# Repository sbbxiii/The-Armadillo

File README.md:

# 🛡️ The Armadillo: Custom ATmega328P + TMC2209 Stepper Motor Controller PCB

---

## 1. Executive Summary

**The Armadillo** is an open-source, Arduino-compatible motion control PCB designed from first principles in **KiCad 10.0.1**. It pairs the reliable **Microchip ATmega328P** 8-bit AVR microcontroller with the high-performance **Trinamic TMC2209-LA** silent bipolar stepper motor driver on a rugged $60.0\text{ mm} \times 60.0\text{ mm}$ 2-layer FR-4 board.

Featuring an onboard **WCH CH340K** USB-to-UART converter with automated DTR auto-reset, The Armadillo provides seamless plug-and-play programming directly through the Arduino IDE, PlatformIO, or AVR-GCC toolchains. Key features include silent stepper motion via **StealthChop2™**, sensorless homing via **StallGuard4™**, dynamic runtime current tuning over a single-wire **PD_UART** interface, and hardware RC-filtered sensor inputs.

---

## 2. 3D Raytraced Visualizations

<p align="center">
  <br>
  <em>Figure 1: Raytraced 3D perspective view of The Armadillo motor controller board showing the ATmega328P core, TMC2209 driver, and screw terminal I/O.</em>
</p>

| Top View (Silicon, Connectors & SMT Layout) | Bottom View (Solid Ground Return & Driver Thermal Vias) |
| :---: | :---: |
|  |  |

---

## 3. Circuit Architecture & Block Diagram

```mermaid
flowchart TD
    subgraph Power_Subsystem ["Power Distribution Network (PDN)"]
        VIN["Motor Power (4.75V - 29V)<br/>Terminal Block J8"] --> BulkCap["Bulk Decoupling<br/>100µF Radial + 2x 100nF"]
        BulkCap --> VMOT["VMOT Supply Rail"]
        VMOT --> LDO["NCP1117-5.0 LDO<br/>(Steps to +5V Logic)"]
        USB["USB Type-B Port (J2)"] --> Schottky["SS14 Schottky Diode (D3)"]
        Schottky --> VCC5["+5V System VCC Rail"]
        LDO --> VCC5
    end

    subgraph MCU_Subsystem ["Microcontroller & Communications"]
        VCC5 --> MCU["ATmega328P-A (TQFP-32)<br/>16.000 MHz Clock"]
        CH340["CH340K USB-UART (U2)"] <-->|"UART RX/TX + DTR Reset"| MCU
        ICSP["6-Pin AVR ISP Header (J1)"] <-->|"SPI MOSI/MISO/SCK/RST"| MCU
        MCU --> LEDS["Power & Diagnostic LEDs<br/>(D1, D2)"]
    end

    subgraph Motion_Subsystem ["Silent Motion Control"]
        VMOT --> TMC["Trinamic TMC2209-LA (U3)<br/>Silent Stepper Driver"]
        VCC5 --> TMC
        MCU -->|"M1_STEP / M1_DIR / EN"| TMC
        MCU <-->|"PD_UART (Single-Wire)"| TMC
        TMC --> SenseRes["Dual 0.11Ω 1210 Sense Resistors<br/>(R13, R14)"]
        TMC --> MotorOut["4-Phase Stepper Terminal (J7)<br/>(A1, A2, B1, B2)"]
    end

    subgraph IO_Subsystem ["Filtered Sensor Inputs"]
        Sensors["Endstops / Sensors (J3 - J6)"] --> RCFilt["RC Low-Pass Filters<br/>(1.5kΩ + 100nF)"]
        RCFilt --> MCU
    end
```

---

## 4. Hardware Specifications & Feature Matrix

### Electrical & Mechanical Metrics
| Specification | Parameter Value | Engineering Notes |
| :--- | :--- | :--- |
| **Board Footprint** | $60.00\text{ mm} \times 60.00\text{ mm}$ | Compact square profile with 3.0 mm radius rounded corners |
| **Mounting Pattern** | 4× M3 Mounting Holes | Positioned at corners for rigid enclosure mounting |
| **Layer Stackup** | 2-Layer FR-4 (1.6 mm thickness) | Top signal/routing + solid bottom GND return plane |
| **Motor Input Voltage ($V_S$)** | **4.75V to 29.0V DC** | Accepts standard 12V or 24V industrial/3D-printer power supplies |
| **Motor Peak Current** | **2.8A Peak / 2.0A RMS** | Configurable in software via TMC2209 internal registers |
| **Current Sense Resistors** | Dual $0.11\ \Omega \pm 1\%$ (1210 SMT) | High power dissipation footprint for thermal stability |
| **Microstepping Modes** | Up to **1/256** | Native 1/16 with MicroPlyer™ interpolation to 1/256 |
| **Microcontroller** | ATmega328P-A (TQFP-32) | 32 KB Flash, 2 KB SRAM, 1 KB EEPROM @ 16 MHz |
| **USB Interface** | CH340K (SSOP-10) | Built-in clock, requires no external crystal |
| **Design Rule Check (DRC)** | **0 Errors, 0 Unconnected Items** | 100% compliant with standard 2-layer PCB fabrication rules |

---

## 5. Trinamic TMC2209 Key Technologies

1. **StealthChop2™**: Voltage-regulated chopper providing completely silent motor movement at low and medium velocities. Eliminates motor whine.
2. **SpreadCycle™**: Highly dynamic current control chopper mode that delivers high torque and precise microstepping at high step frequencies.
3. **StallGuard4™**: Real-time sensorless load measurement that detects mechanical endstops by monitoring motor back-EMF, eliminating mechanical limit switches.
4. **Single-Wire PD_UART**: Allows the ATmega328P to dynamically tune drive current, chopper thresholds, microstep resolution, and read motor diagnostics via one GPIO pin.

---

## 6. Pinout & Peripheral Mapping

### Microcontroller Pin Mapping
| ATmega328P Pin | Net Name | Hardware Function / Target Peripheral |
| :---: | :--- | :--- |
| **Pin 1 (PD3)** | `M1_STEP` | Step pulse command to TMC2209 Pin 16 |
| **Pin 2 (PD4)** | `M1_DIR` | Direction pulse command to TMC2209 Pin 17 |
| **Pin 9 (PB6)** | `XTAL1` | 16.000 MHz Crystal Oscillator ($Y1$) |
| **Pin 10 (PB7)** | `XTAL2` | 16.000 MHz Crystal Oscillator ($Y1$) |
| **Pin 11 (PD5)** | `EN` | Motor output enable/disable (active low) to TMC2209 Pin 18 |
| **Pin 12 (PD6)** | `PD_UART` | Half-duplex single-wire UART communication with TMC2209 Pin 20 |
| **Pin 13 (PD7)** | `DIAGNOSTIC` | StallGuard / fault flag input from TMC2209 Pin 22 |
| **Pin 15 (PB1)** | `DIGITAL_IN1` | Filtered digital input via header $J5$ (RC filtered) |
| **Pin 16 (PB2)** | `DIGITAL_IN2` | Filtered digital input via header $J6$ (RC filtered) |
| **Pin 17 (PB3)** | `MOSI` | SPI Master Out / In-System Programming ($J1$) |
| **Pin 18 (PB4)** | `MISO` | SPI Master In / In-System Programming ($J1$) |
| **Pin 19 (PB5)** | `SCK` | SPI Clock / In-System Programming ($J1$) |
| **Pin 23 (PC0)** | `ANALOG_IN3` | Filtered analog/digital input via header $J3$ |
| **Pin 24 (PC1)** | `ANALOG_IN4` | Filtered analog/digital input via header $J4$ |
| **Pin 29 (PC6)** | `RESET` | Active-low reset tied to tactile switch $SW1$ and CH340K DTR line |
| **Pin 30 (PD0)** | `RXD` (`UART-`) | Hardware UART receive from CH340K USB bridge |
| **Pin 31 (PD1)** | `TXD` (`UART+`) | Hardware UART transmit to CH340K USB bridge |

### External Connectors
| Connector | Type | Net Connections | Function |
| :--- | :--- | :--- | :--- |
| **J1** | 2×3 2.54mm Header | MOSI, MISO, SCK, RESET, VCC, GND | Standard AVR ICSP programming port |
| **J2** | USB Type-B Female | VBUS, D-, D+, GND | PC programming and USB serial communication |
| **J3** | 1×3 2.54mm Header | VCC, `ANALOG_IN3` (filtered), GND | Sensor / Potentiometer input |
| **J4** | 1×3 2.54mm Header | VCC, `ANALOG_IN4` (filtered), GND | Sensor / Limit switch input |
| **J5** | 1×3 2.54mm Header | VCC, `DIGITAL_IN1` (filtered), GND | Optical / Mechanical Endstop input |
| **J6** | 1×3 2.54mm Header | VCC, `DIGITAL_IN2` (filtered), GND | Optical / Mechanical Endstop input |
| **J7** | 4-Pin 2.54mm Screw Terminal | Motor Coils: `A1`, `A2`, `B1`, `B2` | Stepper motor phase output |
| **J8** | 2-Pin 3.5mm Screw Terminal | `VIN` ($4.75\text{V} - 29\text{V}$), `GND` | Main motor power supply input |

---

## 7. Deliverables & Production Assets

| Asset Category | File Path | Description |
| :--- | :--- | :--- |
| **Schematic Vector PDF** | [`schematic/ATmega_TMC2209_Schematic.pdf`](schematic/ATmega_TMC2209_Schematic.pdf) | High-resolution printable schematic |
| **Schematic Vector SVG** | [`schematic/ATmega_TMC2209_Schematic.svg`](schematic/ATmega_TMC2209_Schematic.svg) | Scalable vector graphic of complete circuit |
| **Bill of Materials** | [`manufacturing/ATmega_TMC2209_BOM.csv`](manufacturing/ATmega_TMC2209_BOM.csv) | Full component list with footprints and quantities |
| **Fabrication Package** | [`manufacturing/ATmega_TMC2209_Gerbers_Rev1.zip`](manufacturing/ATmega_TMC2209_Gerbers_Rev1.zip) | Production gerbers & Excellon drill file |
| **KiCad 10 Project** | [`hardware/`](hardware/) | Native `.kicad_pro`, `.kicad_sch`, and `.kicad_pcb` CAD files |

---

## 8. Author & License

* **Designed & Engineered by:** Osakwe Nmesoma Chukwukadibia ([@sbbxiii](https://github.com/sbbxiii))
* **License:** [MIT License](LICENSE)

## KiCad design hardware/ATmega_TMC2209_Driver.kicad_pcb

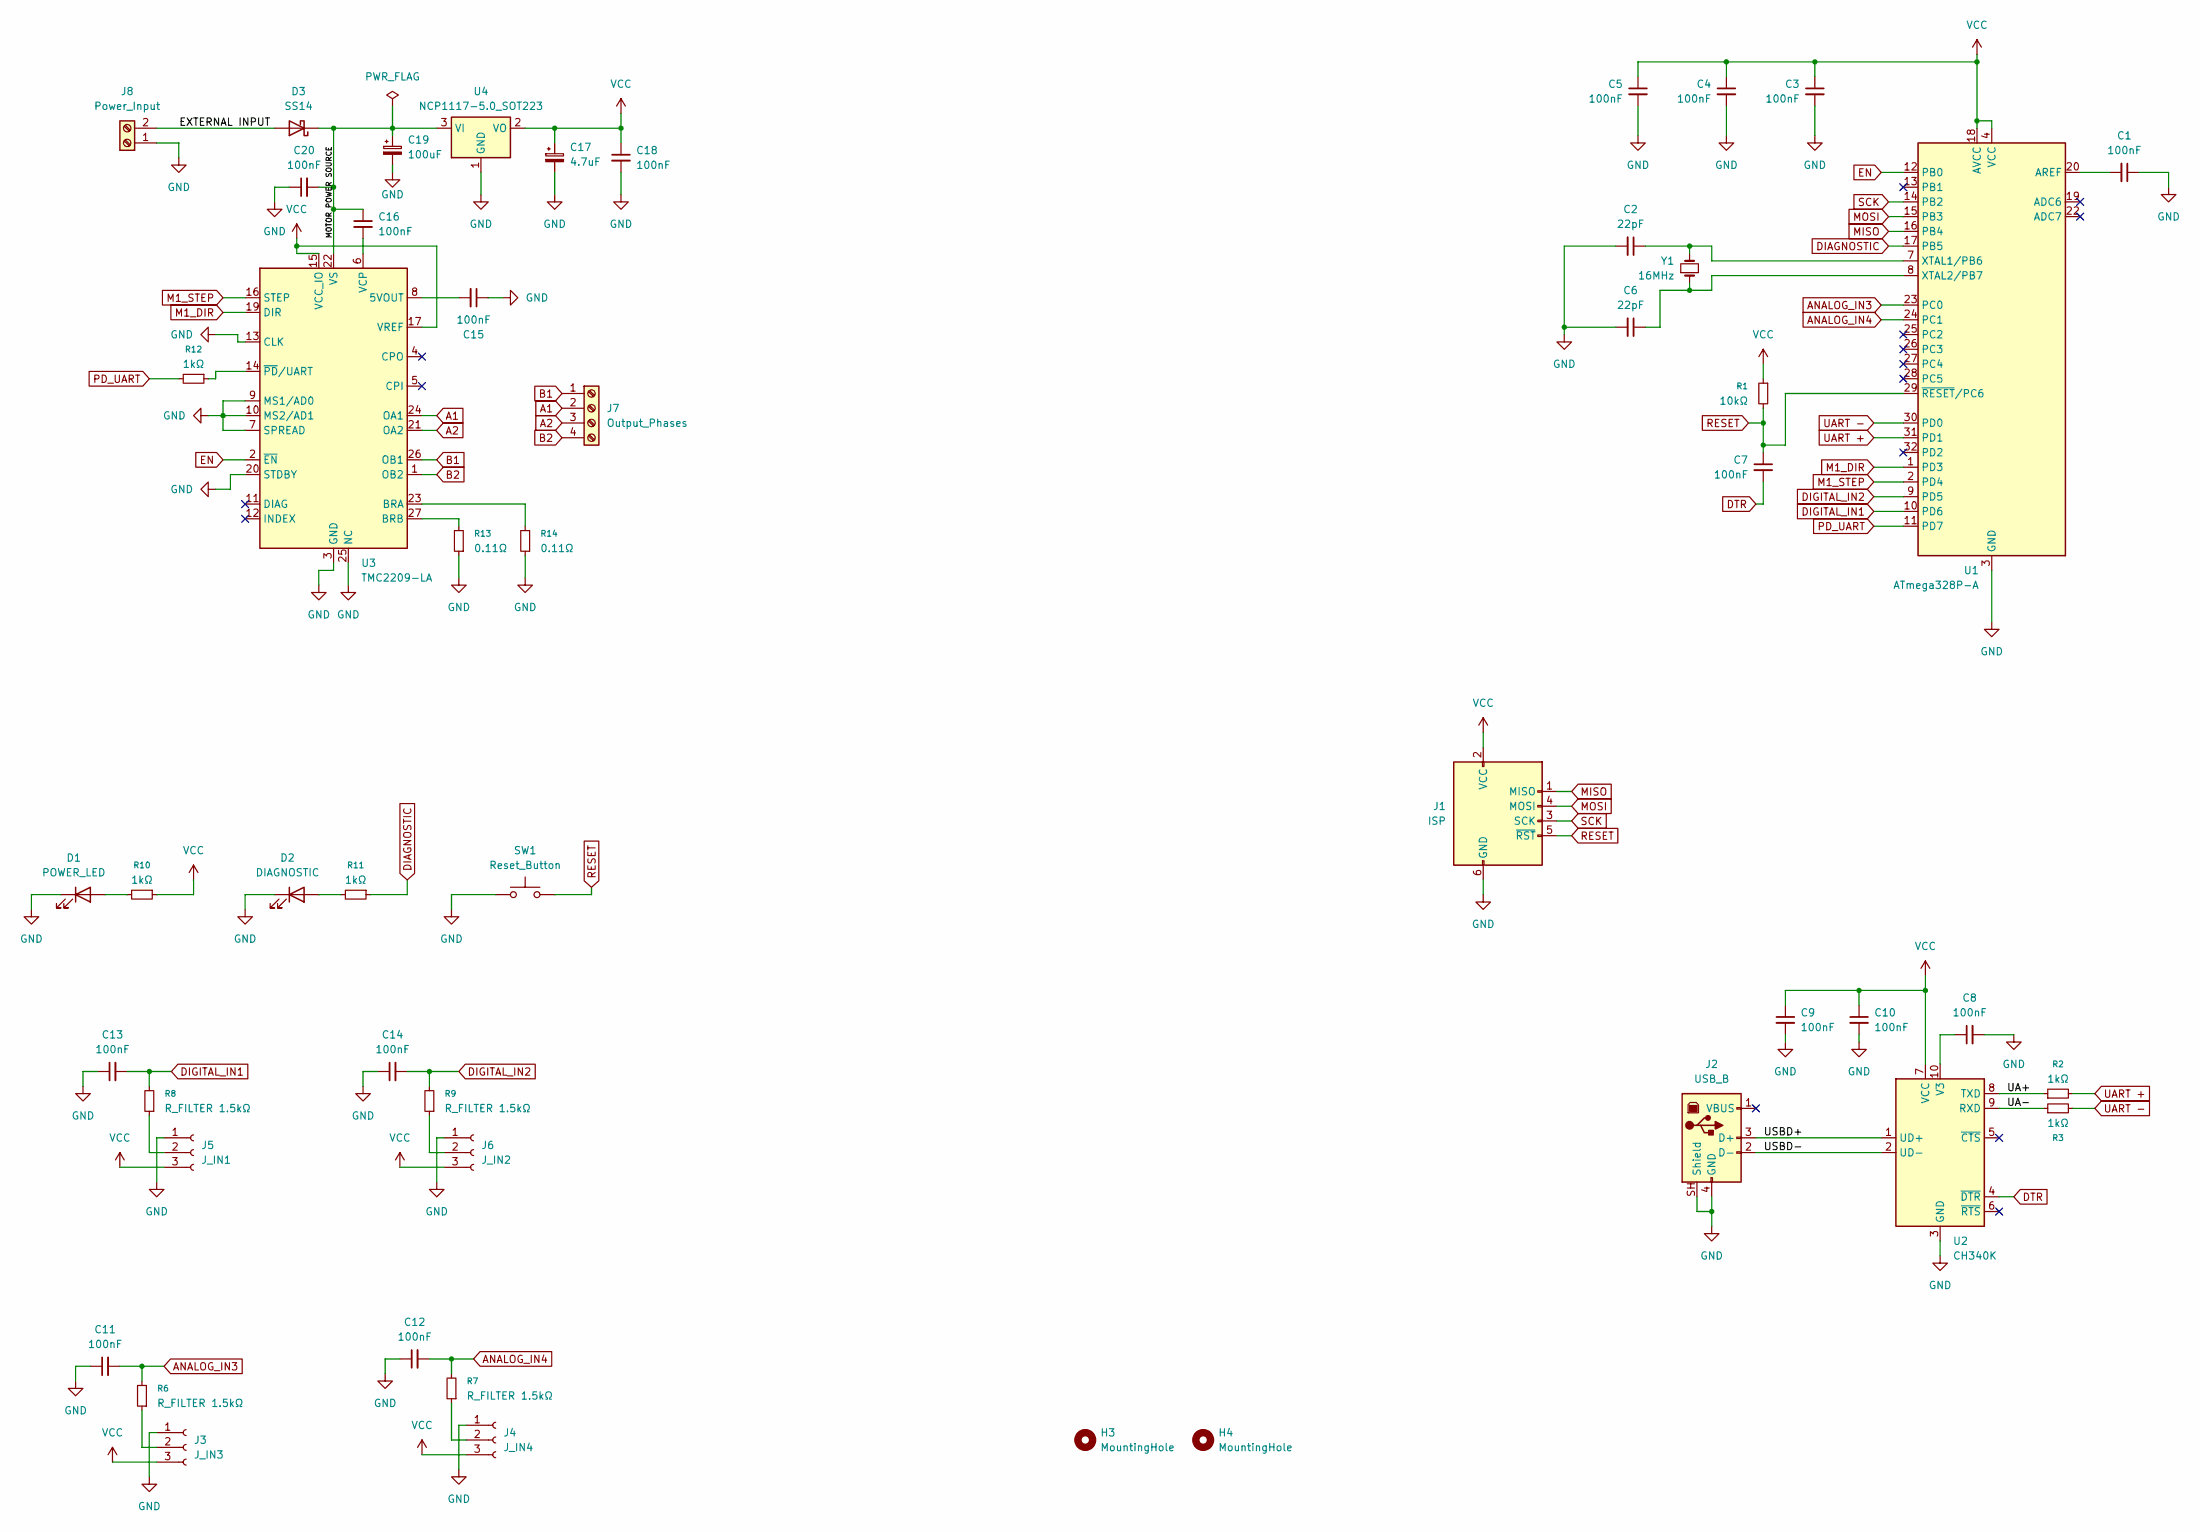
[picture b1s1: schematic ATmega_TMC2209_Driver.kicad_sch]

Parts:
C1, C3, C4, C5, C7, C8, C9, C10, C11, C12, C13, C14, C15, C16, C18, C20: 100nF; C_0805_2012Metric
C2, C6: 22pF; C_0805_2012Metric
C17: 4.7uF; CP_Elec_4x5.3
C19: 100uF; CP_Radial_D8.0mm_P3.50mm
D1: POWER_LED; LED_0805_2012Metric
D2: DIAGNOSTIC; LED_0805_2012Metric
D3: SS14; D_SMA
H3, H4: MountingHole; MountingHole_2.2mm_M2_Pad
J1: ISP; PinHeader_2x03_P2.54mm_Vertical
J2: USB_B; USB_B_OST_USB-B1HSxx_Horizontal
J3: J_IN3; PinHeader_1x03_P2.54mm_Vertical
J4: J_IN4; PinHeader_1x03_P2.54mm_Vertical
J5: J_IN1; PinHeader_1x03_P2.54mm_Vertical
J6: J_IN2; PinHeader_1x03_P2.54mm_Vertical
J7: Output_Phases; TerminalBlock_Phoenix_MPT-0,5-4-2.54_1x04_P2.54mm_Horizontal
J8: Power_Input; TerminalBlock_Phoenix_PT-1,5-2-3.5-H_1x02_P3.50mm_Horizontal
R1: 10kΩ; R_0805_2012Metric
R2, R3, R10, R11, R12: 1kΩ; R_0805_2012Metric
R6, R7, R8, R9: R_FILTER 1.5kΩ; R_0805_2012Metric
R13, R14: 0.11Ω; R_1210_3225Metric
SW1: Reset_Button; SW_SPST_TS-1088-xR020
U1: ATmega328P-A; TQFP-32_7x7mm_P0.8mm
U2: CH340K; SSOP-10-1EP_3.9x4.9mm_P1mm_EP2.1x3.3mm
U3: TMC2209-LA; VQFN-28-1EP_5x5mm_P0.5mm_EP3.7x3.7mm_ThermalVias
U4: NCP1117-5.0_SOT223; SOT-223-3_TabPin2
Y1: 16MHz; Crystal_SMD_5032-2Pin_5.0x3.2mm

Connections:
/EXTERNAL INPUT: D3.2 (A), J8.2
/MOTOR POWER SOURCE: C16.1, C19.1, C20.2, D3.1 (K), U3.22 (VS), U3.28 (VS), U4.3 (VI)
/UA+: R2.1, U2.8 (TXD)
/UA-: R3.1, U2.9 (RXD)
/USBD+: J2.3 (D+), U2.1 (UD+)
/USBD-: J2.2 (D-), U2.2 (UD-)
A1: J7.2, U3.24 (OA1)
A2: J7.3, U3.21 (OA2)
ANALOG_IN3: C11.2, R6.2, U1.23 (PC0)
ANALOG_IN4: C12.2, R7.2, U1.24 (PC1)
B1: J7.1, U3.26 (OB1)
B2: J7.4, U3.1 (OB2)
DIAGNOSTIC: R11.1, U1.17 (PB5)
DIGITAL_IN1: C13.2, R8.2, U1.10 (PD6)
DIGITAL_IN2: C14.2, R9.2, U1.9 (PD5)
DTR: C7.2, U2.4 (~DTR)
EN: U1.12 (PB0), U3.2 (~EN)
GND: C1.1, C2.2, C3.2, C4.2, C5.2, C6.2, C8.2, C9.2, C10.2, C11.1, C12.1, C13.1, C14.1, C15.1, C17.2, C18.2, C19.2, C20.1, D1.1 (K), D2.1 (K), J1.6 (GND), J2.4 (GND), J2.SH (Shield), J3.1, J4.1, J5.1, J6.1, J8.1, R13.1, R14.1, SW1.1, U1.3 (GND), U1.5 (GND), U1.21 (GND), U2.3 (GND), U2.11 (GND), U3.3 (GND), U3.7 (SPREAD), U3.9 (MS1/AD0), U3.10 (MS2/AD1), U3.13 (CLK), U3.18 (GND), U3.20 (STDBY), U3.25 (NC), U3.29 (GND), U4.1 (GND)
M1_DIR: U1.1 (PD3), U3.19 (DIR)
M1_STEP: U1.2 (PD4), U3.16 (STEP)
MISO: J1.1 (MISO), U1.16 (PB4)
MOSI: J1.4 (MOSI), U1.15 (PB3)
unnamed: D1.2 (A), R10.2
unnamed: D2.2 (A), R11.2
unnamed: J3.2, R6.1
unnamed: J4.2, R7.1
unnamed: J5.2, R8.1
unnamed: J6.2, R9.1
unnamed: C1.2, U1.20 (AREF)
unnamed: C2.1, U1.7 (XTAL1/PB6), Y1.2
unnamed: C6.1, U1.8 (XTAL2/PB7), Y1.1
unnamed: C8.1, U2.10 (V3)
unnamed: C15.2, U3.8 (5VOUT)
unnamed: R14.2, U3.23 (BRA)
unnamed: R13.2, U3.27 (BRB)
unnamed: C16.2, U3.6 (VCP)
unnamed: R12.1, U3.14 (~PD/UART)
PD_UART: R12.2, U1.11 (PD7)
RESET: C7.1, J1.5 (~RST), R1.2, SW1.2, U1.29 (~RESET/PC6)
SCK: J1.3 (SCK), U1.14 (PB2)
UART +: R2.2, U1.31 (PD1)
UART -: R3.2, U1.30 (PD0)
VCC: C3.1, C4.1, C5.1, C9.1, C10.1, C17.1, C18.1, J1.2 (VCC), J3.3, J4.3, J5.3, J6.3, R1.1, R10.1, U1.4 (VCC), U1.6 (VCC), U1.18 (AVCC), U2.7 (VCC), U3.15 (VCC_IO), U3.17 (VREF), U4.2 (VO)

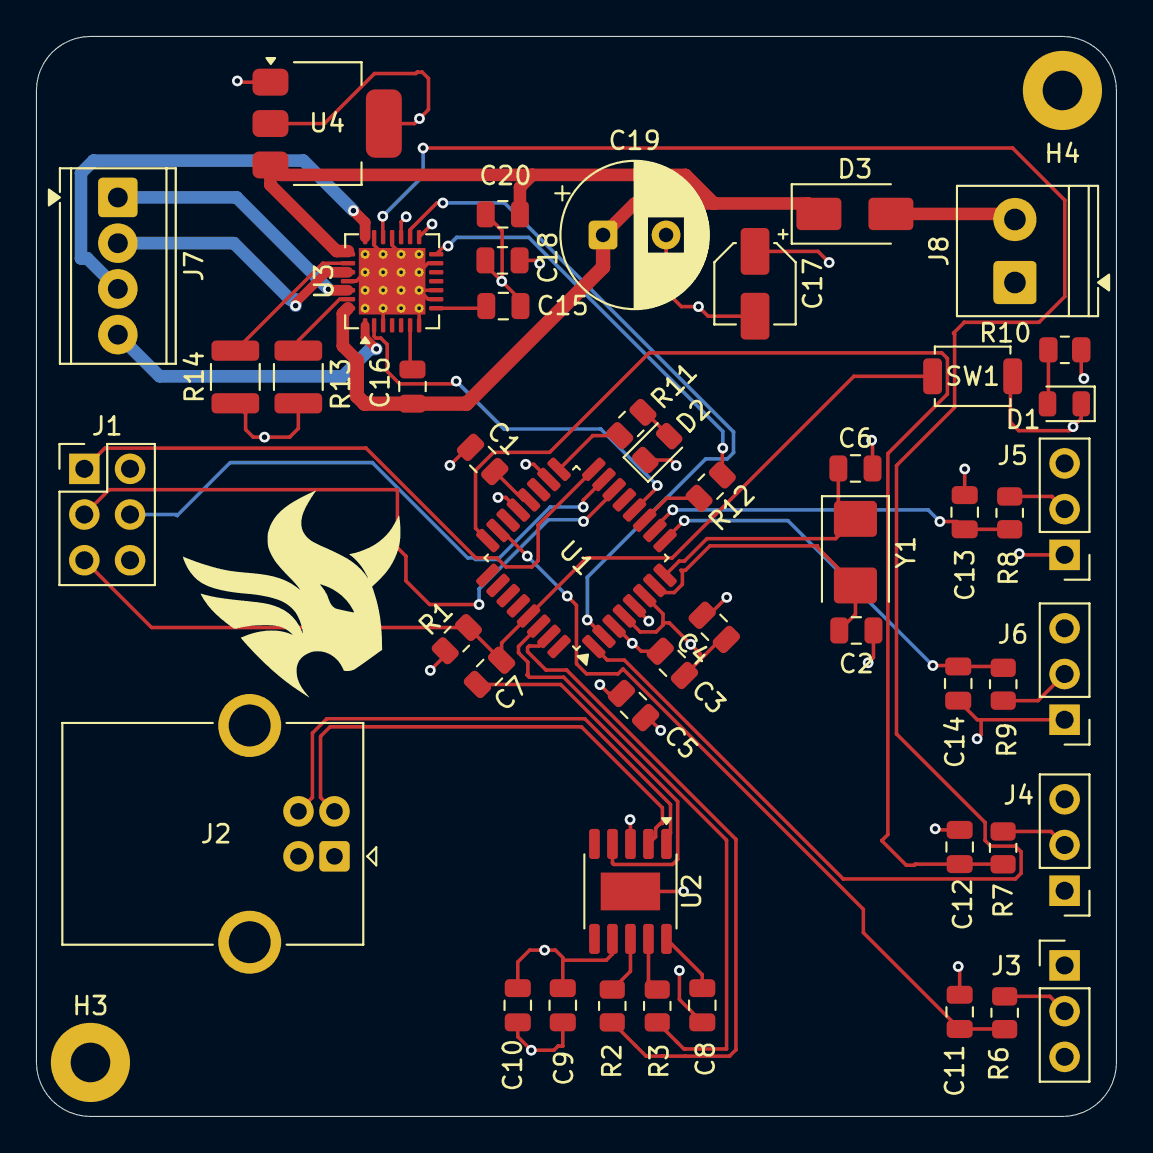
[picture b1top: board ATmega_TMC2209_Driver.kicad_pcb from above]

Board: 4 copper layers, 60.0 x 60.0 mm, 51 parts (0 on the bottom side), 43 nets.

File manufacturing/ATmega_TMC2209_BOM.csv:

"Refs","Value","Footprint","Qty","DNP"
"C1","100nF","Capacitor_SMD:C_0805_2012Metric","1",""
"C2","22pF","Capacitor_SMD:C_0805_2012Metric","1",""
"C3","100nF","Capacitor_SMD:C_0805_2012Metric","1",""
"C4","100nF","Capacitor_SMD:C_0805_2012Metric","1",""
"C5","100nF","Capacitor_SMD:C_0805_2012Metric","1",""
"C6","22pF","Capacitor_SMD:C_0805_2012Metric","1",""
"C7","100nF","Capacitor_SMD:C_0805_2012Metric","1",""
"C8","100nF","Capacitor_SMD:C_0805_2012Metric","1",""
"C9","100nF","Capacitor_SMD:C_0805_2012Metric","1",""
"C10","100nF","Capacitor_SMD:C_0805_2012Metric","1",""
"C11","100nF","Capacitor_SMD:C_0805_2012Metric","1",""
"C12","100nF","Capacitor_SMD:C_0805_2012Metric","1",""
"C13","100nF","Capacitor_SMD:C_0805_2012Metric","1",""
"C14","100nF","Capacitor_SMD:C_0805_2012Metric","1",""
"C15","100nF","Capacitor_SMD:C_0805_2012Metric","1",""
"C16","100nF","Capacitor_SMD:C_0805_2012Metric","1",""
"C17","4.7uF","Capacitor_SMD:CP_Elec_4x5.3","1",""
"C18","100nF","Capacitor_SMD:C_0805_2012Metric","1",""
"C19","100uF","Capacitor_THT:CP_Radial_D8.0mm_P3.50mm","1",""
"C20","100nF","Capacitor_SMD:C_0805_2012Metric","1",""
"D1","POWER_LED","LED_SMD:LED_0805_2012Metric","1",""
"D2","DIAGNOSTIC","LED_SMD:LED_0805_2012Metric","1",""
"D3","SS14","Diode_SMD:D_SMA","1",""
"J1","ISP","Connector_PinHeader_2.54mm:PinHeader_2x03_P2.54mm_Vertical","1",""
"J2","USB_B","Connector_USB:USB_B_OST_USB-B1HSxx_Horizontal","1",""
"J3","J_IN3","Connector_PinHeader_2.54mm:PinHeader_1x03_P2.54mm_Vertical","1",""
"J4","J_IN4","Connector_PinHeader_2.54mm:PinHeader_1x03_P2.54mm_Vertical","1",""
"J5","J_IN1","Connector_PinHeader_2.54mm:PinHeader_1x03_P2.54mm_Vertical","1",""
"J6","J_IN2","Connector_PinHeader_2.54mm:PinHeader_1x03_P2.54mm_Vertical","1",""
"J7","Output_Phases","TerminalBlock_Phoenix:TerminalBlock_Phoenix_MPT-0,5-4-2.54_1x04_P2.54mm_Horizontal","1",""
"J8","Power_Input","TerminalBlock_Phoenix:TerminalBlock_Phoenix_PT-1,5-2-3.5-H_1x02_P3.50mm_Horizontal","1",""
"R1","10kΩ","Resistor_SMD:R_0805_2012Metric","1",""
"R2","1kΩ","Resistor_SMD:R_0805_2012Metric","1",""
"R3","1kΩ","Resistor_SMD:R_0805_2012Metric","1",""
"R6","R_FILTER 1.5kΩ","Resistor_SMD:R_0805_2012Metric","1",""
"R7","R_FILTER 1.5kΩ","Resistor_SMD:R_0805_2012Metric","1",""
"R8","R_FILTER 1.5kΩ","Resistor_SMD:R_0805_2012Metric","1",""
"R9","R_FILTER 1.5kΩ","Resistor_SMD:R_0805_2012Metric","1",""
"R10","1kΩ","Resistor_SMD:R_0805_2012Metric","1",""
"R11","1kΩ","Resistor_SMD:R_0805_2012Metric","1",""
"R12","1kΩ","Resistor_SMD:R_0805_2012Metric","1",""
"R13","0.11Ω","Resistor_SMD:R_1210_3225Metric","1",""
"R14","0.11Ω","Resistor_SMD:R_1210_3225Metric","1",""
"SW1","Reset_Button","Button_Switch_SMD:SW_SPST_TS-1088-xR020","1",""
"U1","ATmega328P-A","Package_QFP:TQFP-32_7x7mm_P0.8mm","1",""
"U2","CH340K","Package_SO:SSOP-10-1EP_3.9x4.9mm_P1mm_EP2.1x3.3mm","1",""
"U3","TMC2209-LA","Package_DFN_QFN:VQFN-28-1EP_5x5mm_P0.5mm_EP3.7x3.7mm_ThermalVias","1",""
"U4","NCP1117-5.0_SOT223","Package_TO_SOT_SMD:SOT-223-3_TabPin2","1",""
"Y1","16MHz","Crystal:Crystal_SMD_5032-2Pin_5.0x3.2mm","1",""
